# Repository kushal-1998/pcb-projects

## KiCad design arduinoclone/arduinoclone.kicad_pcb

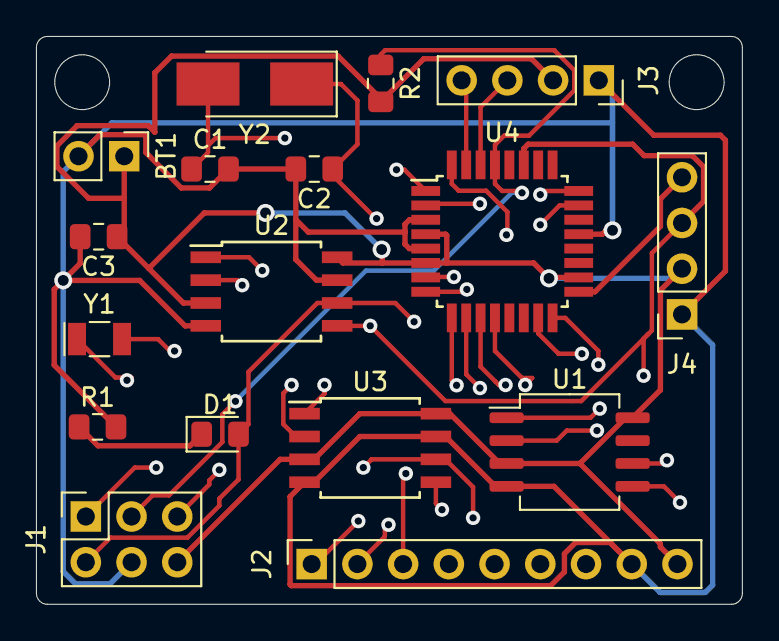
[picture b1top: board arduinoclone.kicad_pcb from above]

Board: 6 copper layers, 39.2 x 31.5 mm, 17 parts (0 on the bottom side), 23 nets.

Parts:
BT1: Battery 3v; PinHeader_1x02_P2.54mm_Vertical
C1, C2: 22pF; C_0805_2012Metric_Pad1.15x1.40mm_HandSolder
C3: 10uf; C_0805_2012Metric_Pad1.15x1.40mm_HandSolder
D1: LED; LED_0805_2012Metric_Pad1.15x1.40mm_HandSolder
J1: ICSP; PinSocket_2x03_P2.54mm_Vertical
J2: digital pins; PinSocket_1x09_P2.54mm_Vertical
J3: serial pins; PinSocket_1x04_P2.54mm_Vertical
J4: I2C; PinSocket_1x04_P2.54mm_Vertical
R1: 330ohm; R_0805_2012Metric_Pad1.15x1.40mm_HandSolder
R2: 10kohm; R_0805_2012Metric_Pad1.15x1.40mm_HandSolder
U1: DS13375+; SO-8_5.3x6.2mm_P1.27mm
U2, U3: 24LC1025; SOIJ-8_5.3x5.3mm_P1.27mm
U4: ATMEGA328P-AU; TQFP-32_7x7mm_P0.8mm
Y1: Crystal 32MHZ; Crystal_SMD_MicroCrystal_CC7V-T1A-2Pin_3.2x1.5mm
Y2: Crystal 16MHZ; Crystal_SMD_5032-2Pin_5.0x3.2mm_HandSoldering

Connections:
/ADDS1: U2.1, U3.1, U4.23
/ADDS2: U2.2, U3.2, U4.24
/D2: J2.1, U4.32
/D3: J2.2, U4.1
/D4: J2.3, U4.2
/D5: J2.4, U4.9
/D6: J2.5, U4.10
/D7: J2.6, U4.11
/D8: J2.7, U4.12
/MISO: J1.1, U4.16
/MOSI: J1.5, U4.15
/RESET: J1.3, R2.1, U4.29
/RX: J3.3, U4.30
/SCK: D1.2, J1.2, J4.4, U1.6, U2.6, U3.6, U4.17
/SDA: J4.3, U1.5, U2.5, U3.5, U4.27
/TX: J3.4, U4.31
/VCC: BT1.1, C3.1, J1.6, J2.9, J3.2, J4.2, R2.2, U1.3, U1.8, U2.3, U2.8, U3.3, U3.8, U4.4, U4.6, U4.18, U4.20
GNDPWR: BT1.2, C1.2, C2.2, C3.2, J1.4, J2.8, J3.1, J4.1, R1.2, U1.4, U2.4, U2.7, U3.4, U3.7, U4.3, U4.5, U4.21
unnamed: C1.1, U4.7, Y2.2
unnamed: C2.1, U4.8, Y2.1
unnamed: D1.1, R1.1
unnamed: U1.1, Y1.2
unnamed: U1.2, Y1.1

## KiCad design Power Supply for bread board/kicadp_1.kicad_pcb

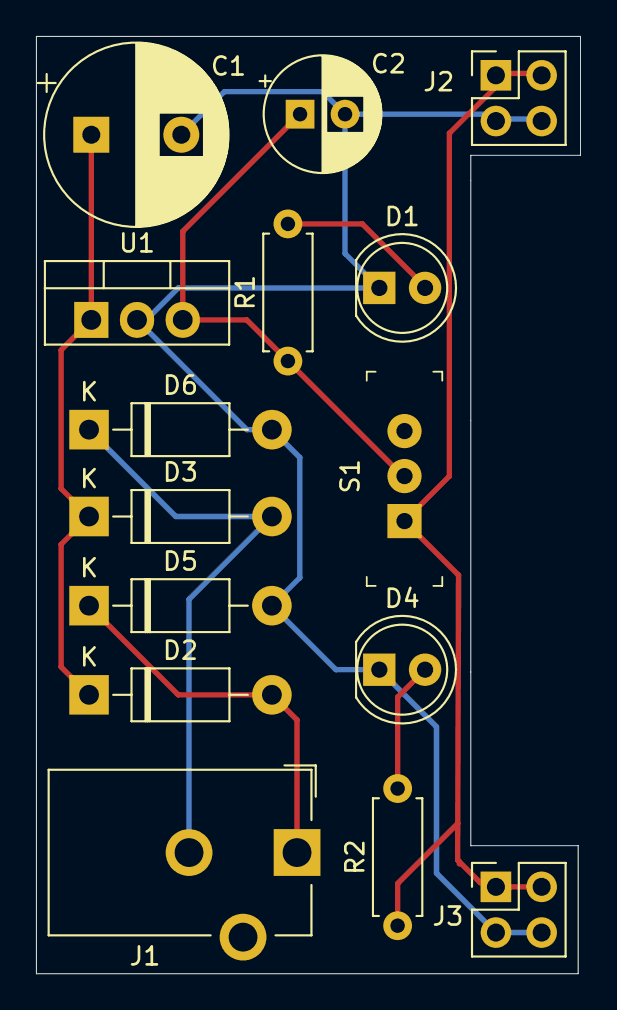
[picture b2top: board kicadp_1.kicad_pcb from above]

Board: 2 copper layers, 30.2 x 52.1 mm, 15 parts (0 on the bottom side), 8 nets.

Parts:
C1: 47uf; CP_Radial_D10.0mm_P5.00mm
C2: 470 uF; CP_Radial_D6.3mm_P2.50mm
D1, D4: LED; LED_D5.0mm
D2, D3, D5, D6: 1N4007; D_DO-41_SOD81_P10.16mm_Horizontal
J1: Barrel_Jack_Switch; BarrelJack_CUI_PJ-102AH_Horizontal
J2, J3: Conn_02x02_Odd_Even; PinHeader_2x02_P2.54mm_Vertical
R1, R2: 330 ohm; R_Axial_DIN0207_L6.3mm_D2.5mm_P7.62mm_Horizontal
S1: EG1218; Switch_Slide_11.6x4mm_EG1218
U1: LM7805_TO220; TO-220-3_Vertical

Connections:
/Vout1: C2.1, R1.1, S1.2, U1.3
/Vout2: J2.1, J2.2, J3.1, J3.2, R2.1, S1.1
/v-: C1.2, C2.2, D1.1, D4.1, D5.2, D6.2, J2.3, J2.4, J3.3, J3.4, U1.2
/vin: C1.1, D2.1, D3.1, U1.1
unnamed: D1.2, R1.2
unnamed: D2.2, D5.1, J1.1
unnamed: D3.2, D6.1, J1.2
unnamed: D4.2, R2.2

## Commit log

2021-05-27 comment
